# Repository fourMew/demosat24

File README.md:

# ACC Demosat 2024 - Closed chamber O3 testing
A low budget payload for testing the effect of fluorocarbons/fluorocarbon like substances on ozone in the upper atmosphere.
 <br/>
 
# How to use this repo
clone the repo, either by running:
```sh
git clone https://github.com/fourMew/demosat24.git
```
or by downloading and extracting the zip:

## Arduino
To use this sketch you must download and install the [DFRobot_OzoneSensor library](https://codeload.github.com/DFRobot/DFRobot_OzoneSensor/zip/master)

*How do I [install an arduino library](https://www.arduino.cc/en/Guide/Libraries#.UxU8mdzF9H0)?*

From here you should be able to open the sketch file demosat24/code/demosat/demosat.ino with the Arduino IDE

This sketch currently supports:

 - Dual O3 sensors via I2C Addresses **0x73** and **0x72**
 - 1 SSCDANN150PGAA5 5v pressure sensor via analog pin **A3**
 - 1 3.3v temp sensor via analog pin **A0**

## KiCAD
With KiCAD, just open the project file demosat24/pcb/shield/demosatShield.kicad_pro

If you get errors or parts of the schematic are not showing up, ensure that the symbols and footprints in the project specific library are properly loaded

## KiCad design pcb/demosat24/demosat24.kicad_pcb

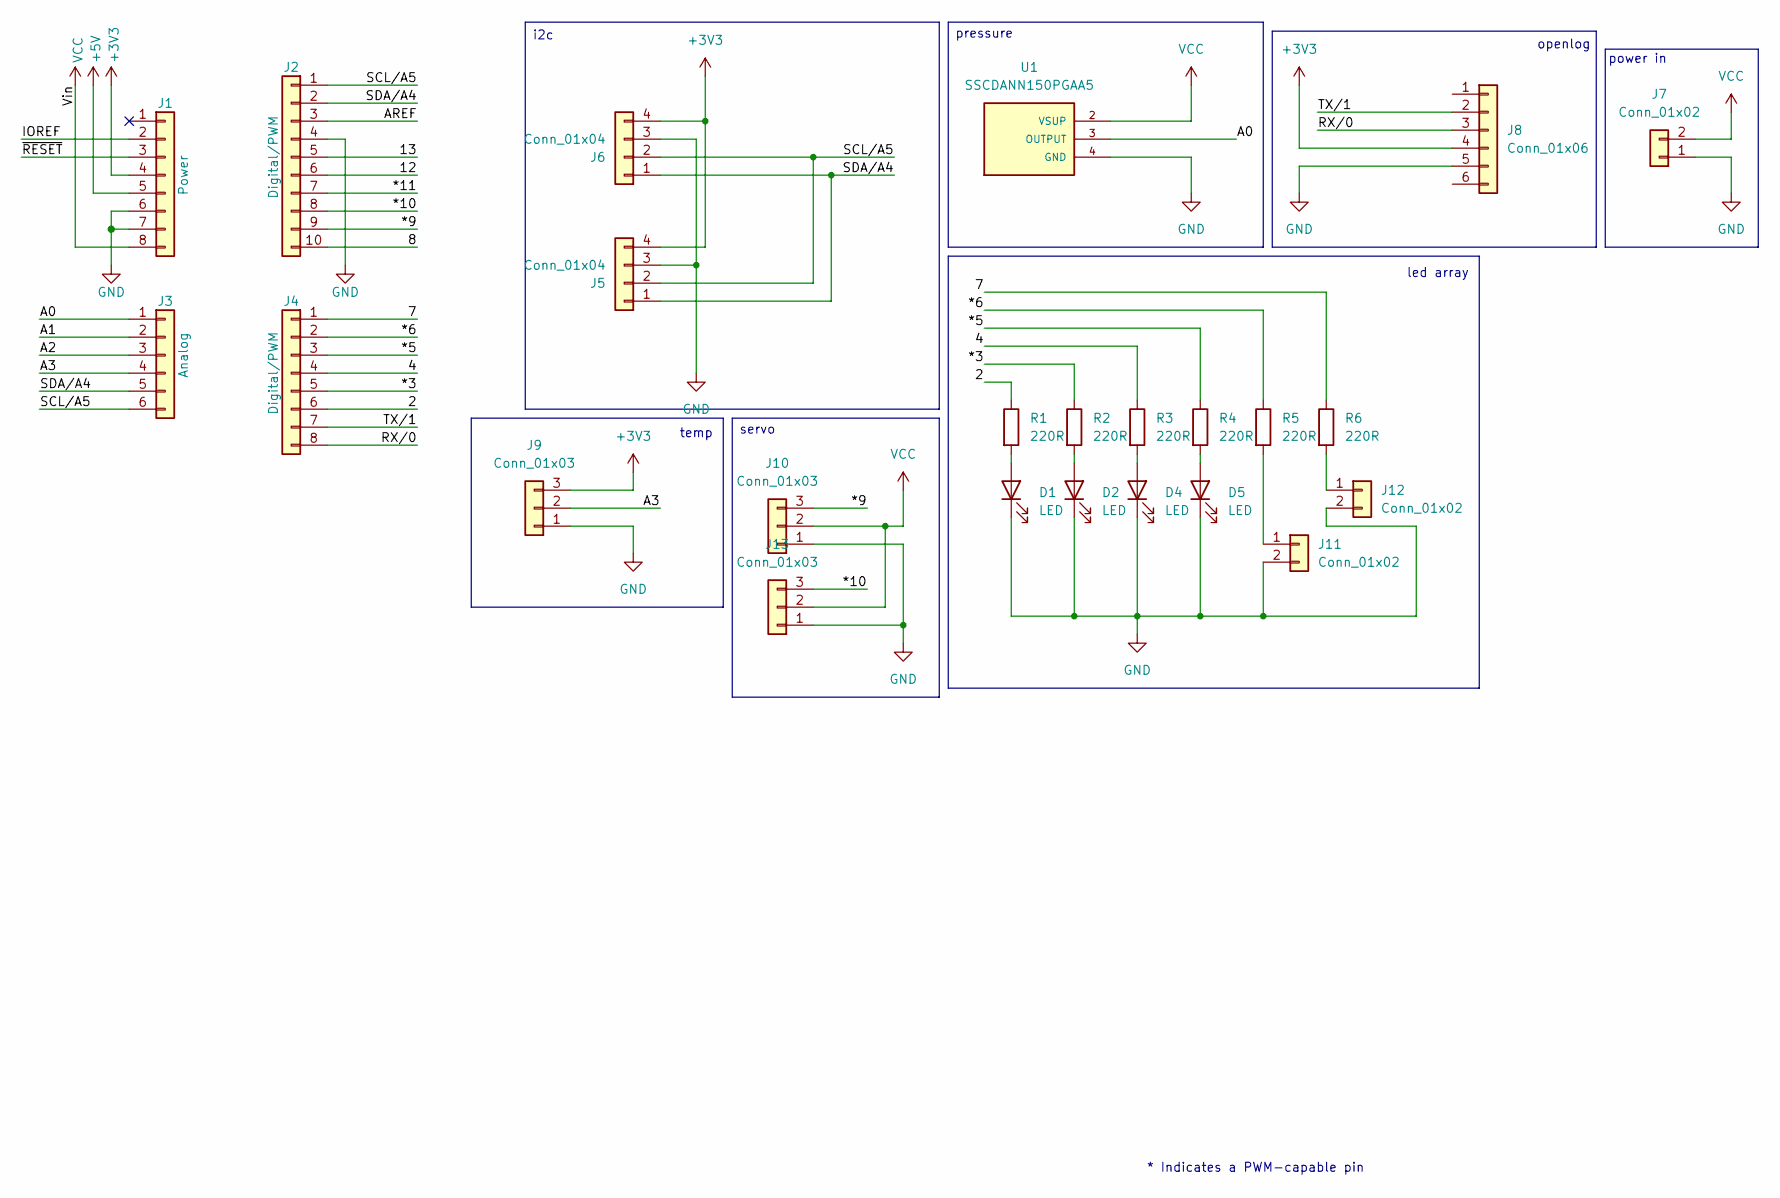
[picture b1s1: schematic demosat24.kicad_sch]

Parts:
D1, D2, D4, D5: LED; LED_D5.0mm
J1: Power; PinSocket_1x08_P2.54mm_Vertical
J2: Digital/PWM; PinSocket_1x10_P2.54mm_Vertical
J3: Analog; PinSocket_1x06_P2.54mm_Vertical
J4: Digital/PWM; PinSocket_1x08_P2.54mm_Vertical
J5, J6: Conn_01x04; JST_PH_S4B-PH-K_1x04_P2.00mm_Horizontal
J7: Conn_01x02; JST_PH_B2B-PH-K_1x02_P2.00mm_Vertical
J8: Conn_01x06; PinSocket_1x06_P2.54mm_Vertical
J9: Conn_01x03; Molex_SL_171971-0003_1x03_P2.54mm_Vertical
J10, J13: Conn_01x03; PinHeader_1x03_P2.54mm_Vertical
J11, J12: Conn_01x02; PinHeader_1x02_P2.54mm_Vertical
R1, R2, R3, R4, R5, R6: 220R; R_Axial_DIN0207_L6.3mm_D2.5mm_P7.62mm_Horizontal
U1: SSCDANN150PGAA5; XDCR_SSCDANN150PGAA5

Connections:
+3V3: J1.4, J5.4, J6.4, J8.4, J9.3
+5V: J1.5
/2: J4.6, R1.1
/4: J4.4, R3.1
/7: J4.1, R6.1
/8: J2.10
/12: J2.6
/13: J2.5
/*3: J4.5, R2.1
/*5: J4.3, R4.1
/*6: J4.2, R5.1
/*9: J2.9, J10.3
/*10: J2.8, J13.3
/*11: J2.7
/A0: J3.1, U1.3 (OUTPUT)
/A1: J3.2
/A2: J3.3
/A3: J3.4, J9.2
/AREF: J2.3
/IOREF: J1.2
/RX/0: J4.8, J8.3
/SCL/A5: J2.1, J3.6, J5.2, J6.2
/SDA/A4: J2.2, J3.5, J5.1, J6.1
/TX/1: J4.7, J8.2
/~RESET: J1.3
GND: D1.1 (K), D2.1 (K), D4.1 (K), D5.1 (K), J1.6, J1.7, J2.4, J5.3, J6.3, J7.1, J8.5, J9.1, J10.1, J11.2, J12.2, J13.1, U1.4 (GND)
unnamed: D1.2 (A), R1.2
unnamed: D2.2 (A), R2.2
unnamed: D4.2 (A), R3.2
unnamed: D5.2 (A), R4.2
unnamed: J11.1, R5.2
unnamed: J12.1, R6.2
VCC: J1.8, J7.2, J10.2, J13.2, U1.2 (VSUP)

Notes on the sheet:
pressure
led array
servo
temp
power in
* Indicates a PWM-capable pin
i2c
openlog

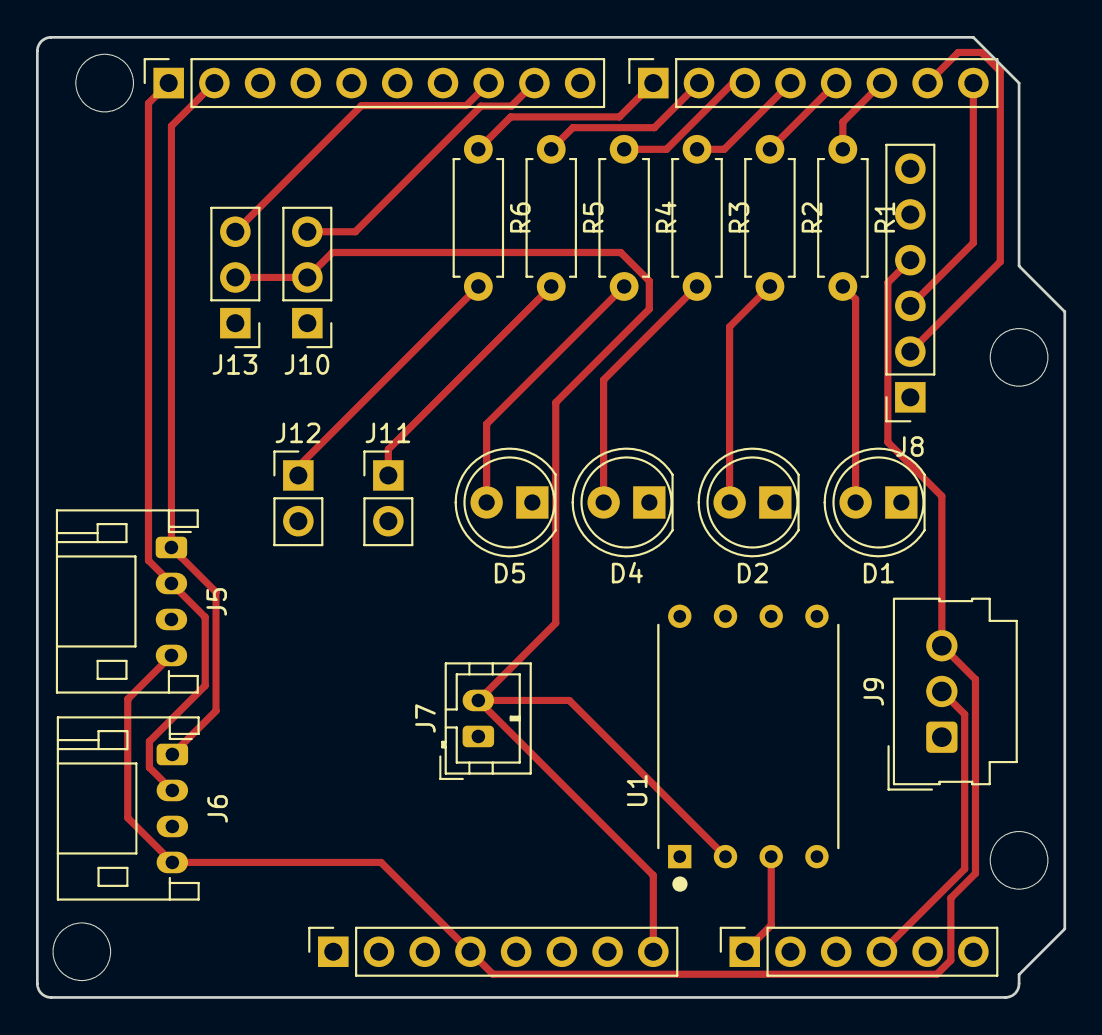
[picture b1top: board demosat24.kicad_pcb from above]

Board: 2 copper layers, 57.1 x 53.3 mm, 28 parts (0 on the bottom side), 23 nets.

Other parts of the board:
MH1, MH2, MH3, MH4: MountingHole_3.2mm

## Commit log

2024-03-13 Update README.md
    Added a basic readme
2024-03-13 Update README.md
    updated screenshot in readme
2024-03-13 Added current Arduino sketch with support for analog pressure and temp, and dual o3 over i2c
2024-03-13 updated readme with sketch info
2024-03-13 Update README.md
    fixed bad readme change
2024-03-13 Update README.md
    made readme maybe slightly clearer
2024-03-13 updated kicad project: schematic for sensors
2024-03-13 kicad: cleaned up, moved all leds to the lower digital header, added socket for openlog
2024-03-14 new kicad project file: new schematic started, pcb started in the new project file
2024-03-14 reorganized schematic slightly
2024-03-18 complete schematic added
2024-03-19 pcb with one servo, all data and power connected but not ground
2024-03-19 minor changes to pcb
2024-03-20 PCB Ordered! switched to dual layer board with ground plane added headers for a second servo cleaned up repo
2024-03-20 new 1 layer pcb layout
2024-03-26 updated pcb design with information learned from assembling the board
